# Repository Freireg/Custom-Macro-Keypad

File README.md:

# Custom-Macro-Keypad
Custom macro mechanical keypad using a ESP32

# Index
- [Overview](#overview)
- [Hardware](#hardware)
- [Firmware](#firmware)
- [Applications](#applications)
# Overview
This projects intends to make a custom keyboard with bluetooth connection using an ESP32 W-ROOM. 
It can have a number of custom configuration and even a Wi-fi setup to work with IoT devices. But, this first implementation will focus on a macro-keyboard setup.
# Hardware
Needed hardware:
> - ESP32 W-ROOM
> - Cherry Mechanical Keys
> - Incremental Enconder (part number: EN12-HN22AF25)
> - RGB LED (part number: 598-8610-307F)
> - Battery charging module / Voltage Regulator (PartNumber: J5019)
> - LiPo Battery (3.7V / 2450mAh)

Schematics and PCB layout can be found in the ["Nano-keyboard" Folder](https://github.com/Freireg/Custom-Macro-Keypad/tree/main/Nano-keyboard)

# Firmware
## Library
## How to read a button matrix
# Applications

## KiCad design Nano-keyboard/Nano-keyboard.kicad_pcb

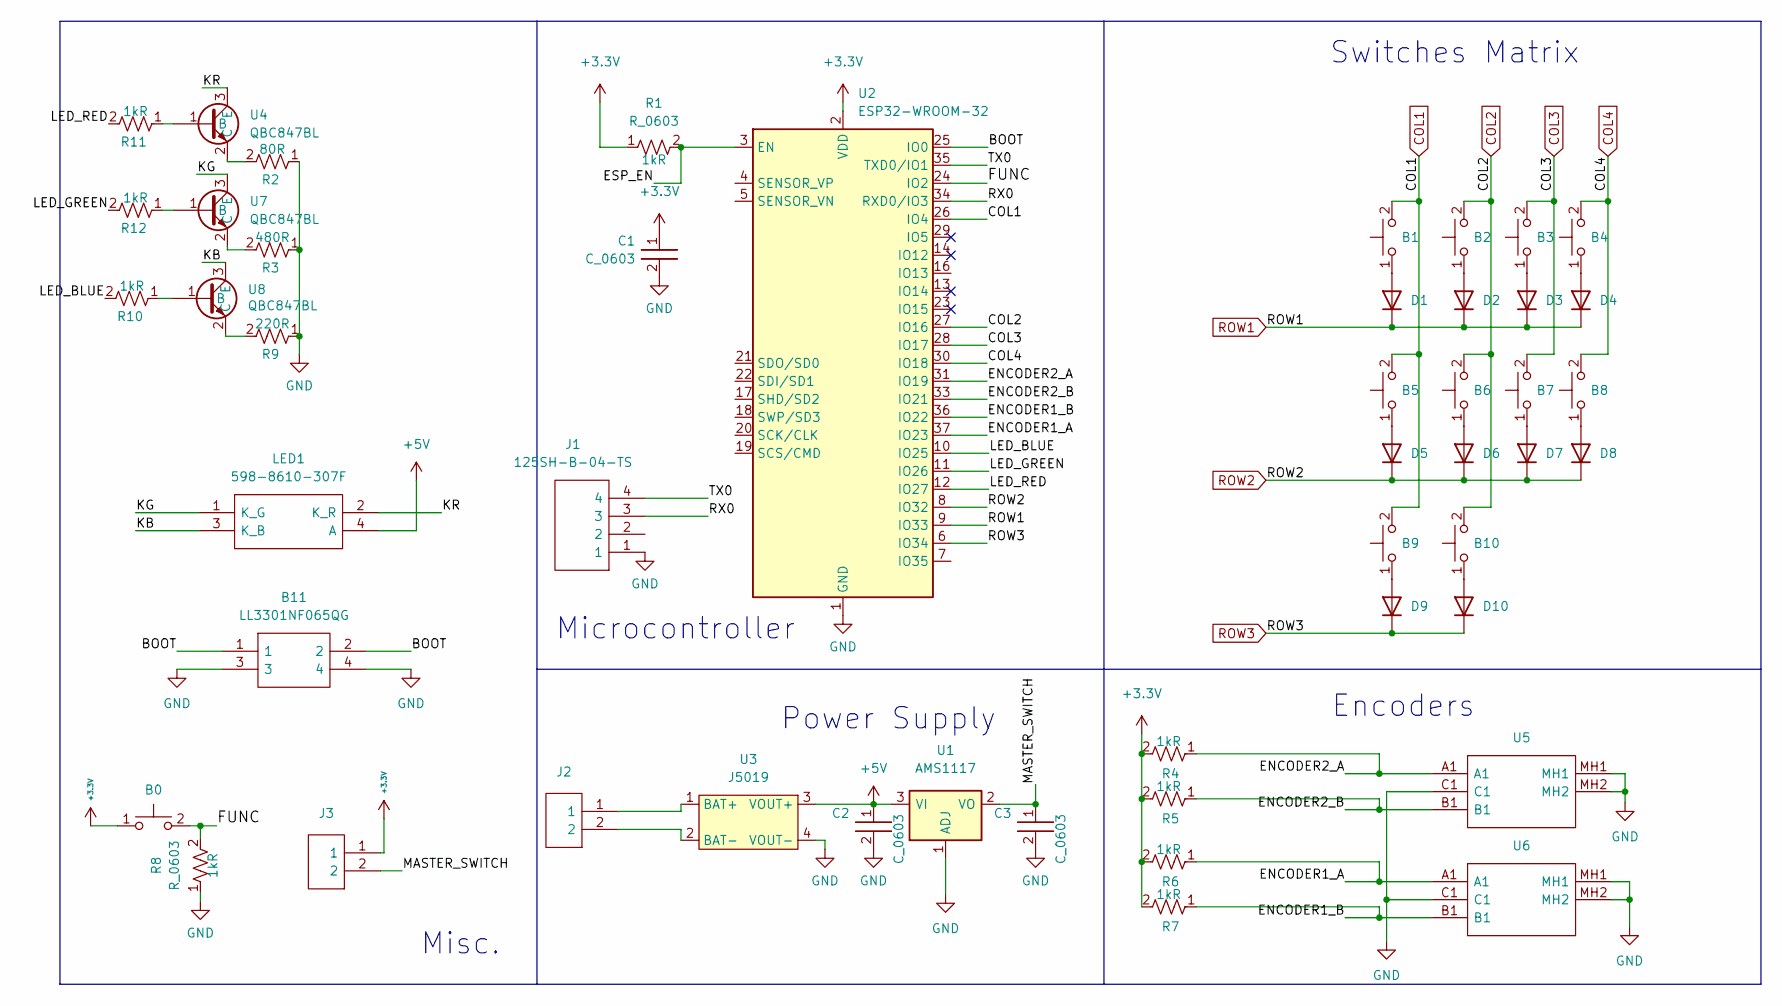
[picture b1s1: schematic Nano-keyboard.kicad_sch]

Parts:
B0, B1, B2, B3, B4, B5, B6, B7, B8, B9, B10: Cherry_Switch_1U_PCB; SW_Cherry_MX_1.00u_PCB
B11: LL3301NF065QG; Manufacturer_Part_Number LL3301NF065QG; Mouser Part Number 612-LL3301NF065QG
C1, C2, C3: C_0603; C_0603_1608Metric
D1, D2, D3, D4, D5, D6, D7, D8, D9, D10: 1N914; D_DO-35_SOD27_P7.62mm_Horizontal
J1: 125SH-B-04-TS; SHDR4W35P0X125_1X4_800X320X420P; Manufacturer_Part_Number 125SH-B-04-TS
J2, J3: 25SH-B-02-TS; 25SHB02TS; Manufacturer_Part_Number 125SH-B-02-TS
LED1: 598-8610-307F; 5988610307F; Manufacturer_Part_Number 598-8610-307F; Mouser Part Number 645-598-8610-307F
R1, R2, R3, R4, R5, R6, R7, R8, R9, R10, R11, R12: R_0603; R_0603_1608Metric
U1: AMS1117; SOT-223-3_TabPin2
U2: ESP32-WROOM-32
U3: J5019; J5019-module
U4, U7, U8: QBC847BL; SOT96P237X111-3N
U5, U6: EN12-HN22AF25; EN12HN22AF25; Manufacturer_Part_Number EN12-HN22AF25; Mouser Part Number 858-EN12-HN22AF25

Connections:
+3V3: B0.1, C1.1, J3.1, R1.1, R4.2, R5.2, R6.2, R7.2, U2.2 (VDD)
/BOOT: B11.1, B11.2, U2.25 (IO0)
/ENCODER1_A: R6.1, U2.37 (IO23), U6.A1
/ENCODER1_B: R7.1, U2.36 (IO22), U6.B1
/ENCODER2_A: R4.1, U2.31 (IO19), U5.A1
/ENCODER2_B: R5.1, U2.33 (IO21), U5.B1
/ESP_EN: R1.2, U2.3 (EN)
/FUNC: B0.2, R8.2, U2.24 (IO2)
/KB: LED1.3 (K_B), U8.3 (E)
/KG: LED1.1 (K_G), U7.3 (E)
/KR: LED1.2 (K_R), U4.3 (E)
/LED_BLUE: R10.2, U2.10 (IO25)
/LED_GREEN: R12.2, U2.11 (IO26)
/LED_RED: R11.2, U2.12 (IO27)
/MASTER_SWITCH: C3.1, J3.2, U1.2 (VO)
/RX0: J1.3, U2.34 (RXD0/IO3)
/TX0: J1.4, U2.35 (TXD0/IO1)
COL1: B1.2, B5.2, B9.2, U2.26 (IO4)
COL2: B2.2, B6.2, B10.2, U2.27 (IO16)
COL3: B3.2, B7.2, U2.28 (IO17)
COL4: B4.2, B8.2, U2.30 (IO18)
GND: B11.3, B11.4, C1.2, C2.2, C3.2, J1.1, R2.1, R3.1, R8.1, R9.1, U1.1 (ADJ), U2.1 (GND), U2.15 (GND), U2.38 (GND), U2.39 (GND), U3.4 (VOUT-), U5.C1, U5.MH1, U5.MH2, U6.C1, U6.MH1, U6.MH2
unnamed: B1.1, D1.2 (A)
unnamed: B2.1, D2.2 (A)
unnamed: B3.1, D3.2 (A)
unnamed: B4.1, D4.2 (A)
unnamed: B5.1, D5.2 (A)
unnamed: B6.1, D6.2 (A)
unnamed: B7.1, D7.2 (A)
unnamed: B8.1, D8.2 (A)
unnamed: B9.1, D9.2 (A)
unnamed: B10.1, D10.2 (A)
unnamed: J2.1, U3.1 (BAT+)
unnamed: J2.2, U3.2 (BAT-)
unnamed: R2.2, U4.2 (C)
unnamed: R3.2, U7.2 (C)
unnamed: R9.2, U8.2 (C)
unnamed: R10.1, U8.1 (B)
unnamed: R11.1, U4.1 (B)
unnamed: R12.1, U7.1 (B)
ROW1: D1.1 (K), D2.1 (K), D3.1 (K), D4.1 (K), U2.9 (IO33)
ROW2: D5.1 (K), D6.1 (K), D7.1 (K), D8.1 (K), U2.8 (IO32)
ROW3: D9.1 (K), D10.1 (K), U2.6 (IO34)

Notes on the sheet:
Microcontroller
Power Supply
Encoders
Misc.
Switches Matrix

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
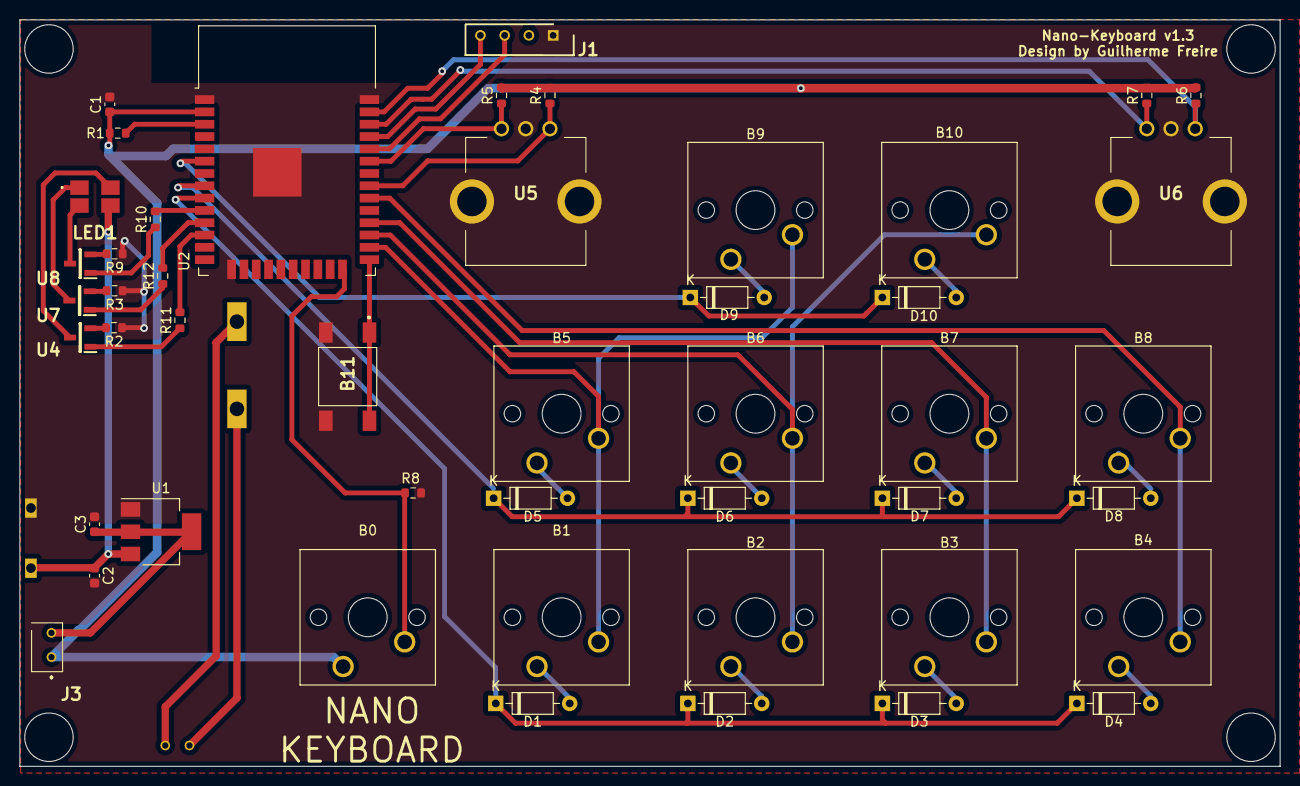
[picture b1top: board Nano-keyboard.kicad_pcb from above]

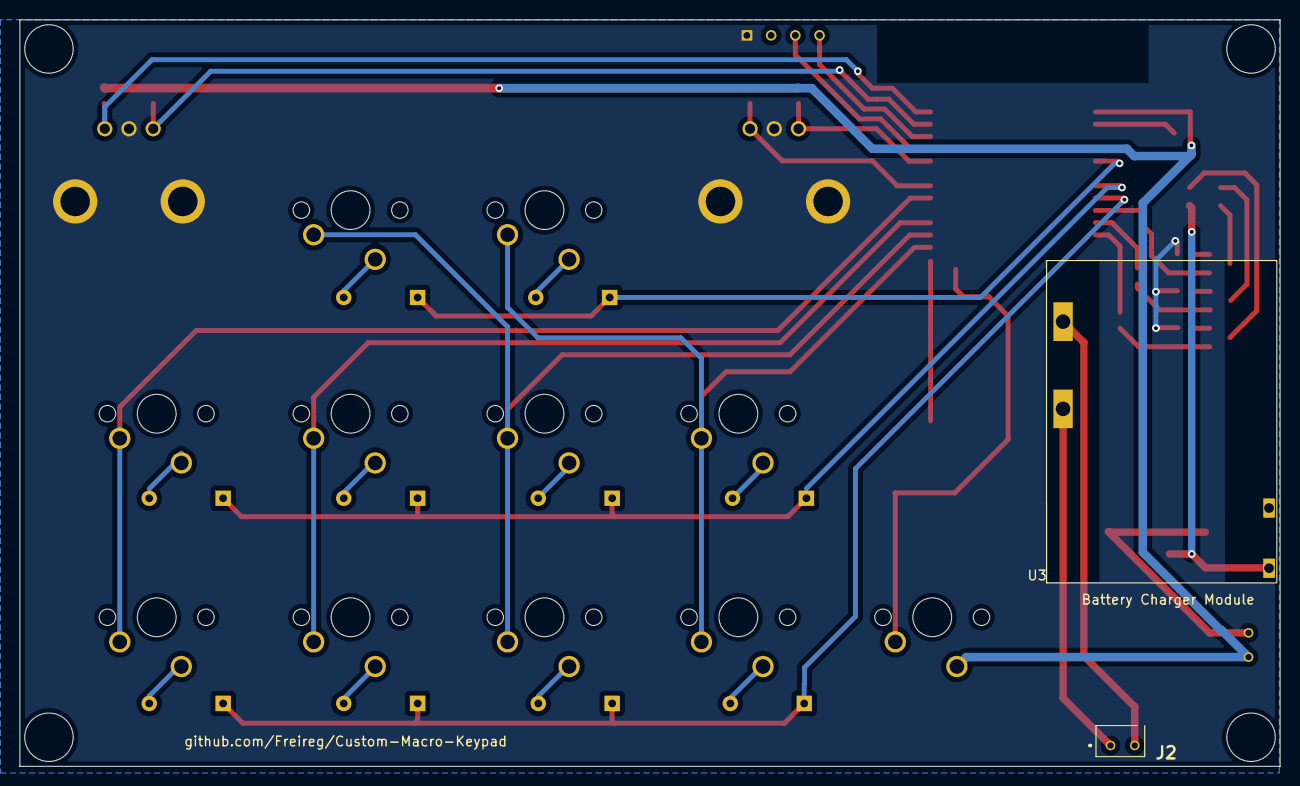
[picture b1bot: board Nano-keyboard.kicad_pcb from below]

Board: 2 copper layers, 130.0 x 77.0 mm, 49 parts (2 on the bottom side), 44 nets.

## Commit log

2022-06-10 First layout design
2022-06-13 ESP initial changes
2022-06-13 Minor schematic changes
2022-06-13 3D Switch Models
2022-06-13 Minor changes
2022-06-20 Reference
2022-06-28 Diode Changes
2022-07-01 Charger Module and keyboard layout changes
2022-07-02 Layout changes
2022-07-05 Adding gitignore
2022-07-05 Initial routing
2022-07-06 Added Resistors and Capacitor
2022-07-07 Routing changes
2022-07-08 Routing Done [Pending Revision]
2022-07-08 Added RGB leds
2022-07-09 First firmware iteration
2022-07-11 Board Dimensions changes
2022-07-14 3D model updates
2022-07-15 Footprint adjustmetns
2022-07-28 Adjusting J5019 footprint
2022-07-29 added BJTs
2022-07-30 Routing of version 1.2 almest finished
2022-08-02 Finished Routing
2022-08-02 Gerber file update
2022-08-02 Minor update
2022-08-03 Encoder default application
2022-08-09 PCB V1.2 test firmware
2022-08-12 First Keyboard commands set working
2022-08-12 RGB Led not working
2022-08-12 Pinout change
2022-08-12 Addded more spacing between keys and encoder
2022-08-16 Minor adjustments
2022-08-16 [Firmware] Minor updates
2022-08-18 [hardware update]
2022-09-26 [Layout] LED 5V Supply
2022-11-04 [Firmware] Encoder not properly working
2022-11-08 [Firmware] Encoder working
2022-11-11 [Software] First software interaction
2022-11-11 Merged again
2023-02-07 Including shortcuts
2023-03-09 Code refatoring
2023-03-09 readMatrix function
2023-03-15 Blekeyboard press function can use a char
2023-03-15 Deafult functions and layout
2023-03-16 Default macros changes
2023-08-04 Not yet tested
2023-10-21 Including LED blinks and special shortcuts
